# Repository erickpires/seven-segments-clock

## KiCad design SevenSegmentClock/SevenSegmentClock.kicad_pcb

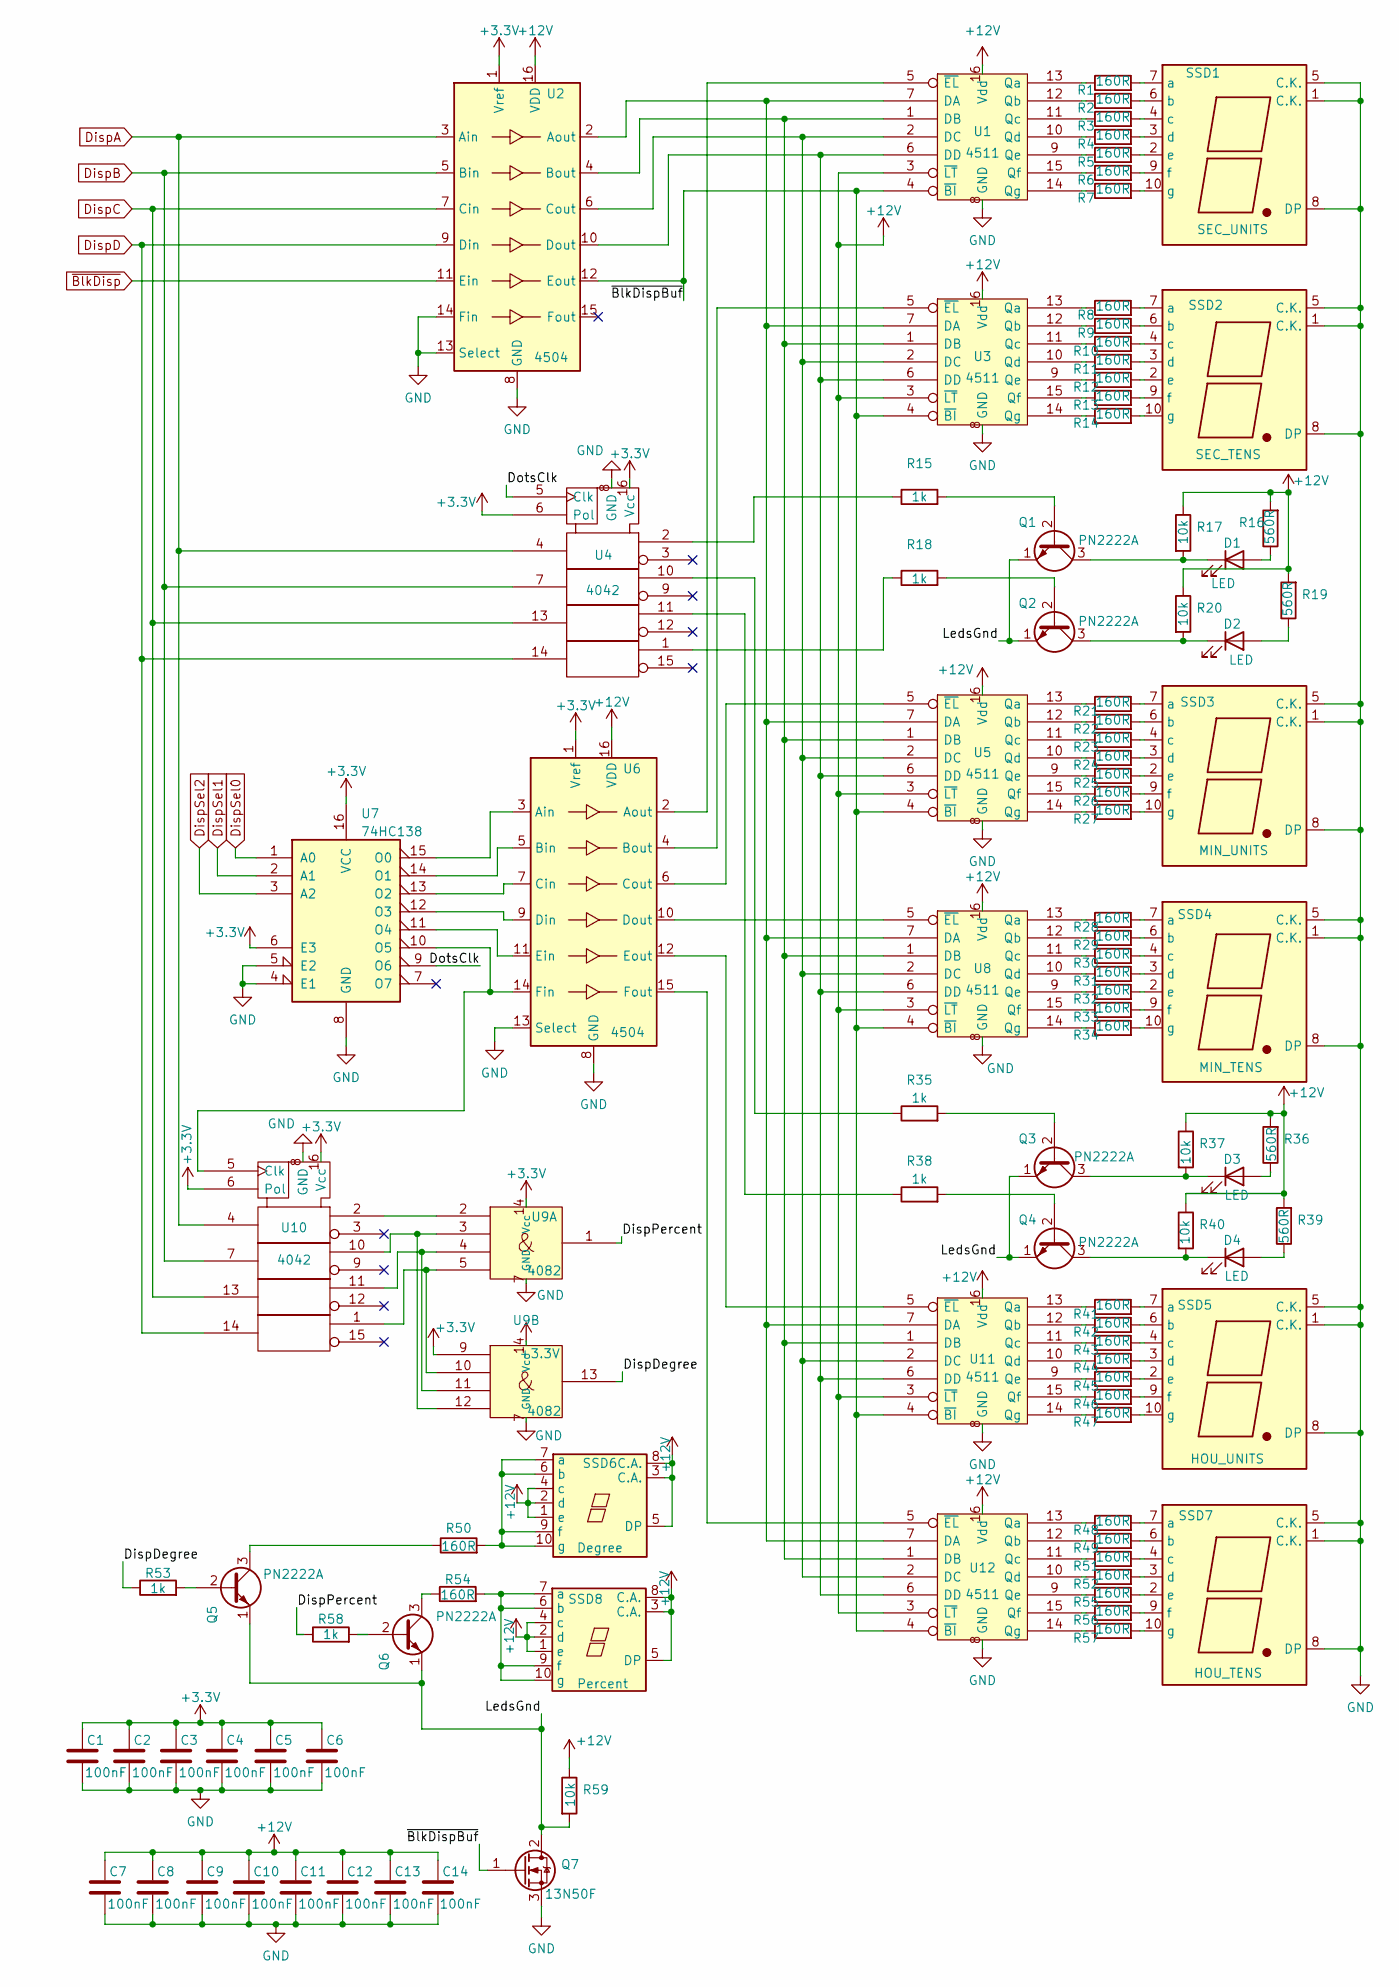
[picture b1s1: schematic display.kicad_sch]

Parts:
C1, C2, C3, C4, C5, C6, C7, C8, C9, C10, C11, C12, C13, C14: 100nF; C_1206_3216Metric_Pad1.33x1.80mm_HandSolder
D1, D2, D3, D4: LED; LED_D5.0mm
Q1, Q2, Q3, Q4, Q5, Q6: PN2222A; TO-92_Inline
Q7: 13N50F; TO-220-3_Vertical
R1, R2, R3, R4, R5, R6, R7, R8, R9, R10, R11, R12, R13, R14, R21, R22, R23, R24, R25, R26, R27, R28, R29, R30, R31, R32, R33, R34, R41, R42, R43, R44, R45, R46, R47, R48, R49, R50, R51, R52, R54, R55, R56, R57: 160R; R_1206_3216Metric_Pad1.30x1.75mm_HandSolder
R15, R18, R35, R38, R53, R58: 1k; R_1206_3216Metric_Pad1.30x1.75mm_HandSolder
R16, R19, R36, R39: 560R; R_Axial_DIN0207_L6.3mm_D2.5mm_P10.16mm_Horizontal
R17, R20, R37, R40, R59: 10k; R_Axial_DIN0207_L6.3mm_D2.5mm_P10.16mm_Horizontal
SSD1: SEC_UNITS; LSD230A
SSD2: SEC_TENS; LSD230A
SSD3: MIN_UNITS; LSD230A
SSD4: MIN_TENS; LSD230A
SSD5: HOU_UNITS; LSD230A
SSD6: Degree; 7SegmentLED_LTS6760_LTS6780
SSD7: HOU_TENS; LSD230A
SSD8: Percent; 7SegmentLED_LTS6760_LTS6780
U1, U3, U5, U8, U11, U12: 4511; SOIC-16_3.9x9.9mm_P1.27mm
U2, U6: 4504; SOIC-16_3.9x9.9mm_P1.27mm
U4, U10: 4042; DIP-16_W7.62mm_Socket_LongPads
U7: 74HC138; SOIC-16_3.9x9.9mm_P1.27mm
U9: 4082; DIP-14_W7.62mm_Socket_LongPads

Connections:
+3.3V: C1.1, C2.1, C3.1, C4.1, C5.1, C6.1, U2.1 (Vref), U4.6 (Pol), U4.16 (Vcc), U6.1 (Vref), U7.6 (E3), U7.16 (VCC), U9.9, U9.14 (Vcc), U10.6 (Pol), U10.16 (Vcc); also elsewhere on the board
+12V: C7.1, C8.1, C9.1, C10.1, C11.1, C12.1, C13.1, C14.1, R16.2, R17.1, R19.2, R20.1, R36.2, R37.1, R39.2, R40.1, R59.1, SSD6.1 (e), SSD6.2 (d), SSD6.3 (C.A.), SSD6.4 (c), SSD6.5 (DP), SSD6.8 (C.A.), SSD8.1 (e), SSD8.2 (d), SSD8.3 (C.A.), SSD8.4 (c), SSD8.5 (DP), SSD8.8 (C.A.), U1.3 (~LT), U1.16 (Vdd), U2.16 (VDD), U3.3 (~LT), U3.16 (Vdd), U5.3 (~LT), U5.16 (Vdd), U6.16 (VDD), U8.3 (~LT), U8.16 (Vdd), U11.3 (~LT), U11.16 (Vdd), U12.3 (~LT), U12.16 (Vdd); also elsewhere on the board
/Display/DotsClk: U4.5 (Clk), U7.9 (O6)
/Display/LedsGnd: Q1.1 (E), Q2.1 (E), Q3.1 (E), Q4.1 (E), Q5.1 (E), Q6.1 (E), Q7.2 (D), R59.2
/Display/~BlkDispBuf: Q7.1 (G), U1.4 (~BI), U2.12 (Eout), U3.4 (~BI), U5.4 (~BI), U8.4 (~BI), U11.4 (~BI), U12.4 (~BI)
DispA: U2.3 (Ain), U4.4, U10.4; also elsewhere on the board
DispB: U2.5 (Bin), U4.7, U10.7; also elsewhere on the board
DispC: U2.7 (Cin), U4.13, U10.13; also elsewhere on the board
DispD: U2.9 (Din), U4.14, U10.14; also elsewhere on the board
DispSel0: U7.1 (A0); also elsewhere on the board
DispSel1: U7.2 (A1); also elsewhere on the board
DispSel2: U7.3 (A2); also elsewhere on the board
GND: C1.2, C2.2, C3.2, C4.2, C5.2, C6.2, C7.2, C8.2, C9.2, C10.2, C11.2, C12.2, C13.2, C14.2, Q7.3 (S), SSD1.1 (C.K.), SSD1.5 (C.K.), SSD1.8 (DP), SSD2.1 (C.K.), SSD2.5 (C.K.), SSD2.8 (DP), SSD3.1 (C.K.), SSD3.5 (C.K.), SSD3.8 (DP), SSD4.1 (C.K.), SSD4.5 (C.K.), SSD4.8 (DP), SSD5.1 (C.K.), SSD5.5 (C.K.), SSD5.8 (DP), SSD7.1 (C.K.), SSD7.5 (C.K.), SSD7.8 (DP), U1.8 (GND), U2.8 (GND), U2.13 (Select), U2.14 (Fin), U3.8 (GND), U4.8 (GND), U5.8 (GND), U6.8 (GND), U6.13 (Select), U7.4 (E1), U7.5 (E2), U7.8 (GND), U8.8 (GND), U9.7 (GND), U10.8 (GND), U11.8 (GND), U12.8 (GND); also elsewhere on the board
unnamed: D1.1 (K), Q1.3 (C), R17.2
unnamed: D1.2 (A), R16.1
unnamed: D2.1 (K), Q2.3 (C), R20.2
unnamed: D2.2 (A), R19.1
unnamed: D3.1 (K), Q3.3 (C), R37.2
unnamed: D3.2 (A), R36.1
unnamed: D4.1 (K), Q4.3 (C), R40.2
unnamed: D4.2 (A), R39.1
unnamed: Q1.2 (B), R15.2
unnamed: Q2.2 (B), R18.2
unnamed: Q3.2 (B), R35.2
unnamed: Q4.2 (B), R38.2
unnamed: Q5.2 (B), R53.2
unnamed: Q5.3 (C), R50.1
unnamed: Q6.2 (B), R58.2
unnamed: Q6.3 (C), R54.1
unnamed: R1.1, U1.13 (Qa)
unnamed: R1.2, SSD1.7 (a)
unnamed: R2.1, U1.12 (Qb)
unnamed: R2.2, SSD1.6 (b)
unnamed: R3.1, U1.11 (Qc)
unnamed: R3.2, SSD1.4 (c)
unnamed: R4.1, U1.10 (Qd)
unnamed: R4.2, SSD1.3 (d)
unnamed: R5.1, U1.9 (Qe)
unnamed: R5.2, SSD1.2 (e)
unnamed: R6.1, U1.15 (Qf)
unnamed: R6.2, SSD1.9 (f)
unnamed: R7.1, U1.14 (Qg)
unnamed: R7.2, SSD1.10 (g)
unnamed: R8.1, U3.13 (Qa)
unnamed: R8.2, SSD2.7 (a)
unnamed: R9.1, U3.12 (Qb)
unnamed: R9.2, SSD2.6 (b)
unnamed: R10.1, U3.11 (Qc)
unnamed: R10.2, SSD2.4 (c)
unnamed: R11.1, U3.10 (Qd)
unnamed: R11.2, SSD2.3 (d)
unnamed: R12.1, U3.9 (Qe)
unnamed: R12.2, SSD2.2 (e)
unnamed: R13.1, U3.15 (Qf)
unnamed: R13.2, SSD2.9 (f)
unnamed: R14.1, U3.14 (Qg)
unnamed: R14.2, SSD2.10 (g)
unnamed: R15.1, U4.2
unnamed: R18.1, U4.1
unnamed: R21.1, U5.13 (Qa)
unnamed: R21.2, SSD3.7 (a)
unnamed: R22.1, U5.12 (Qb)
unnamed: R22.2, SSD3.6 (b)
unnamed: R23.1, U5.11 (Qc)
unnamed: R23.2, SSD3.4 (c)
unnamed: R24.1, U5.10 (Qd)
unnamed: R24.2, SSD3.3 (d)
unnamed: R25.1, U5.9 (Qe)
unnamed: R25.2, SSD3.2 (e)
unnamed: R26.1, U5.15 (Qf)
unnamed: R26.2, SSD3.9 (f)
unnamed: R27.1, U5.14 (Qg)
unnamed: R27.2, SSD3.10 (g)
unnamed: R28.1, U8.13 (Qa)
unnamed: R28.2, SSD4.7 (a)
unnamed: R29.1, U8.12 (Qb)
unnamed: R29.2, SSD4.6 (b)
unnamed: R30.1, U8.11 (Qc)
unnamed: R30.2, SSD4.4 (c)
unnamed: R31.1, U8.10 (Qd)
unnamed: R31.2, SSD4.3 (d)
unnamed: R32.1, U8.9 (Qe)
unnamed: R32.2, SSD4.2 (e)
unnamed: R33.1, U8.15 (Qf)
unnamed: R33.2, SSD4.9 (f)
unnamed: R34.1, U8.14 (Qg)
unnamed: R34.2, SSD4.10 (g)
unnamed: R35.1, U4.10
unnamed: R38.1, U4.11
unnamed: R41.1, U11.13 (Qa)
unnamed: R41.2, SSD5.7 (a)
unnamed: R42.1, U11.12 (Qb)
unnamed: R42.2, SSD5.6 (b)
unnamed: R43.1, U11.11 (Qc)
unnamed: R43.2, SSD5.4 (c)
unnamed: R44.1, U11.10 (Qd)
unnamed: R44.2, SSD5.3 (d)
unnamed: R45.1, U11.9 (Qe)
unnamed: R45.2, SSD5.2 (e)
unnamed: R46.1, U11.15 (Qf)
unnamed: R46.2, SSD5.9 (f)
unnamed: R47.1, U11.14 (Qg)
unnamed: R47.2, SSD5.10 (g)
unnamed: R48.1, U12.13 (Qa)
unnamed: R48.2, SSD7.7 (a)
unnamed: R49.1, U12.12 (Qb)
unnamed: R49.2, SSD7.6 (b)
unnamed: R50.2, SSD6.6 (b), SSD6.7 (a), SSD6.9 (f), SSD6.10 (g)
unnamed: R51.1, U12.11 (Qc)
unnamed: R51.2, SSD7.4 (c)
unnamed: R52.1, U12.10 (Qd)
unnamed: R52.2, SSD7.3 (d)
unnamed: R54.2, SSD8.6 (b), SSD8.7 (a), SSD8.9 (f), SSD8.10 (g)
unnamed: R55.1, U12.9 (Qe)
unnamed: R55.2, SSD7.2 (e)
unnamed: R56.1, U12.15 (Qf)
unnamed: R56.2, SSD7.9 (f)
unnamed: R57.1, U12.14 (Qg)
unnamed: R57.2, SSD7.10 (g)
unnamed: U1.1 (DB), U2.4 (Bout), U3.1 (DB), U5.1 (DB), U8.1 (DB), U11.1 (DB), U12.1 (DB)
unnamed: U1.2 (DC), U2.6 (Cout), U3.2 (DC), U5.2 (DC), U8.2 (DC), U11.2 (DC), U12.2 (DC)
unnamed: U1.5 (~EL), U6.2 (Aout)
unnamed: U1.6 (DD), U2.10 (Dout), U3.6 (DD), U5.6 (DD), U8.6 (DD), U11.6 (DD), U12.6 (DD)
unnamed: U1.7 (DA), U2.2 (Aout), U3.7 (DA), U5.7 (DA), U8.7 (DA), U11.7 (DA), U12.7 (DA)
unnamed: U3.5 (~EL), U6.4 (Bout)
unnamed: U5.5 (~EL), U6.6 (Cout)
unnamed: U6.3 (Ain), U7.15 (O0)
unnamed: U6.5 (Bin), U7.14 (O1)
unnamed: U6.7 (Cin), U7.13 (O2)
unnamed: U6.9 (Din), U7.12 (O3)
unnamed: U6.10 (Dout), U8.5 (~EL)
unnamed: U6.11 (Ein), U7.11 (O4)
unnamed: U9.5, U9.10, U10.1
unnamed: U9.2, U10.2
unnamed: U6.14 (Fin), U7.10 (O5), U10.5 (Clk)
unnamed: U9.3, U9.12, U10.10
unnamed: U9.4, U9.11, U10.11
unnamed: U6.12 (Eout), U11.5 (~EL)
unnamed: U6.15 (Fout), U12.5 (~EL)
~BlkDisp: U2.11 (Ein); also elsewhere on the board

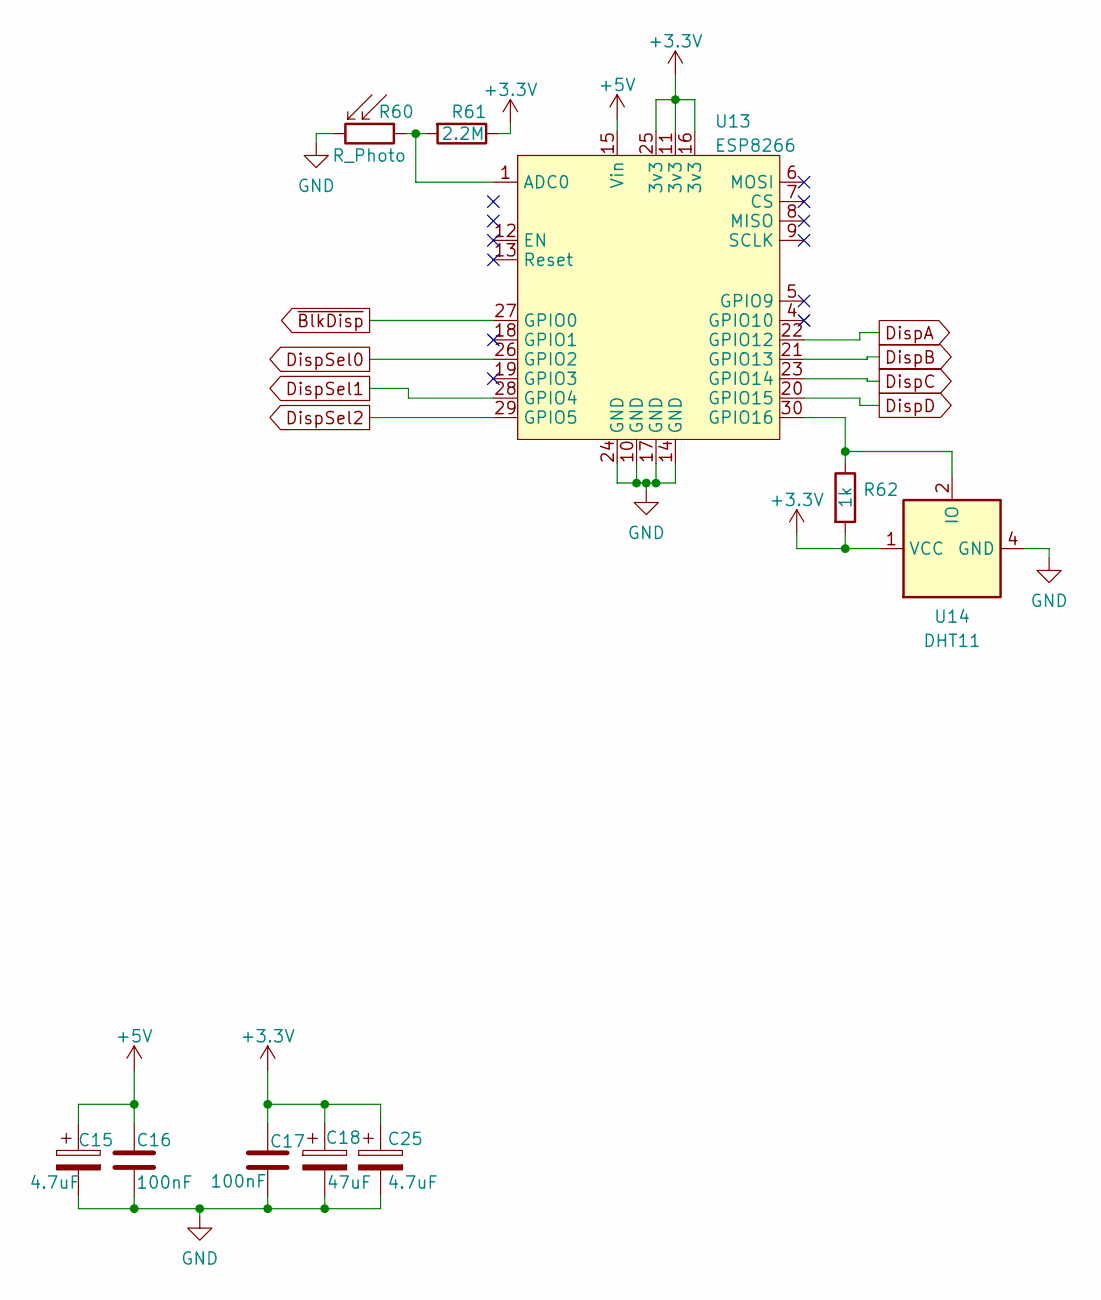
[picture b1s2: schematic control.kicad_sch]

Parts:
C15, C25: 4.7uF; CP_Radial_D6.3mm_P2.50mm
C16, C17: 100nF; C_1206_3216Metric_Pad1.33x1.80mm_HandSolder
C18: 47uF; CP_Radial_D6.3mm_P2.50mm
R60: R_Photo; R_LDR_4.9x4.2mm_P2.54mm_Vertical
R61: 2.2M; R_Axial_DIN0207_L6.3mm_D2.5mm_P10.16mm_Horizontal
R62: 1k; R_1206_3216Metric_Pad1.30x1.75mm_HandSolder
U13: ESP8266; ESP8266 (NodeMCU_12-E)
U14: DHT11; Aosong_DHT11_5.5x12.0_P2.54mm

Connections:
+3.3V: C17.1, C18.1, C25.1, R61.1, R62.2, U13.11 (3v3), U13.16 (3v3), U13.25 (3v3), U14.1 (VCC); also elsewhere on the board
+5V: C15.1, C16.1, U13.15 (Vin); also elsewhere on the board
DispA: U13.22 (GPIO12); also elsewhere on the board
DispB: U13.21 (GPIO13); also elsewhere on the board
DispC: U13.23 (GPIO14); also elsewhere on the board
DispD: U13.20 (GPIO15); also elsewhere on the board
DispSel0: U13.26 (GPIO2); also elsewhere on the board
DispSel1: U13.28 (GPIO4); also elsewhere on the board
DispSel2: U13.29 (GPIO5); also elsewhere on the board
GND: C15.2, C16.2, C17.2, C18.2, C25.2, R60.2, U13.10 (GND), U13.14 (GND), U13.17 (GND), U13.24 (GND), U14.4 (GND); also elsewhere on the board
unnamed: R60.1, R61.2, U13.1 (ADC0)
unnamed: R62.1, U13.30 (GPIO16), U14.2 (IO)
~BlkDisp: U13.27 (GPIO0); also elsewhere on the board

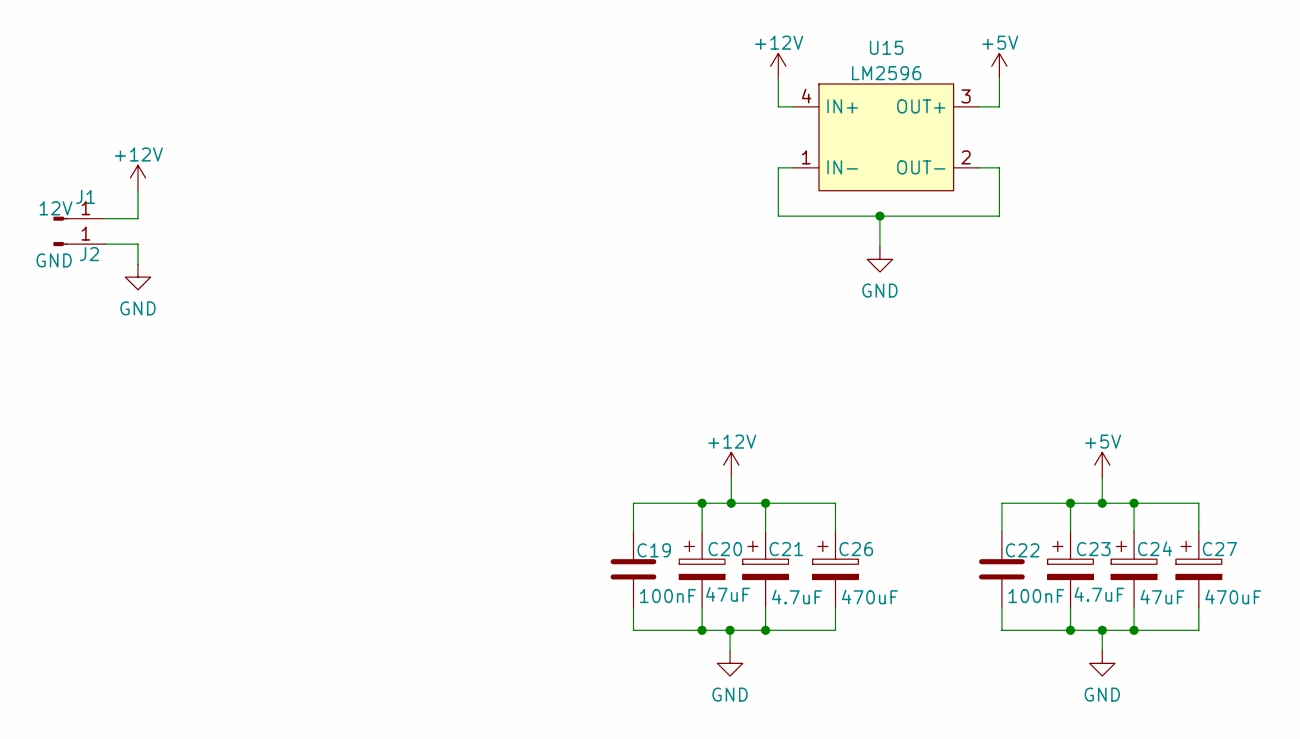
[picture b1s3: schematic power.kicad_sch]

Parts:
C19, C22: 100nF; C_1206_3216Metric_Pad1.33x1.80mm_HandSolder
C20, C24: 47uF; CP_Radial_D6.3mm_P2.50mm
C21, C23: 4.7uF; CP_Radial_D6.3mm_P2.50mm
C26, C27: 470uF; CP_Radial_D10.0mm_P5.00mm
J1: 12V; PinHeader_1x01_P2.54mm_Vertical
J2: GND; PinHeader_1x01_P2.54mm_Vertical
U15: LM2596

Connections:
+5V: C22.1, C23.1, C24.1, C27.1, U15.3 (OUT+); also elsewhere on the board
+12V: C19.1, C20.1, C21.1, C26.1, J1.1, U15.4 (IN+); also elsewhere on the board
GND: C19.2, C20.2, C21.2, C22.2, C23.2, C24.2, C26.2, C27.2, J2.1, U15.1 (IN-), U15.2 (OUT-); also elsewhere on the board

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
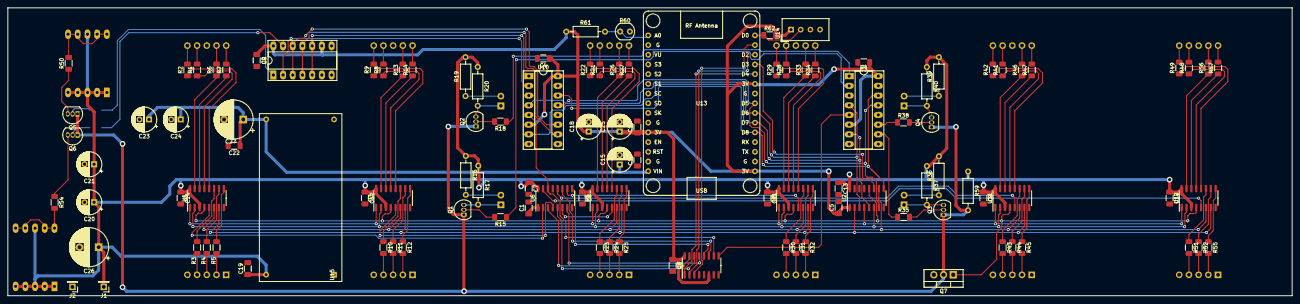
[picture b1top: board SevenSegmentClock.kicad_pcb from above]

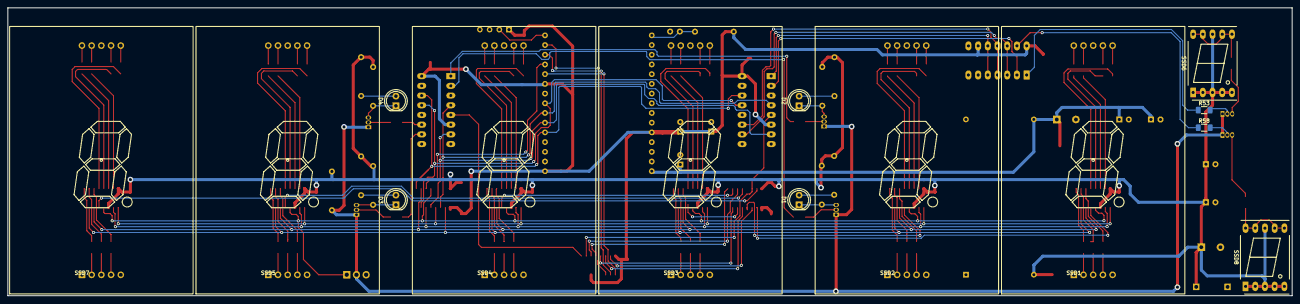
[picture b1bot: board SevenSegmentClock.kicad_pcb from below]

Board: 2 copper layers, 336.1 x 75.3 mm, 125 parts (14 on the bottom side), 145 nets.

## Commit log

2023-02-06 Starting schematic
2024-02-11 NTP code
2024-02-11 Updating BOM
2024-02-11 Modifying code to use direct port manipulation
2024-02-11 Implementing the comunication with the DHT11
2024-02-11 WIP: Configuration server
2024-02-11 Assigning footprints
2024-02-11 Moving the display code to a separate file
2024-02-11 Adding the control schematic and fixing Eletrical Rules Checks
2024-02-11 Adding two more displays to show a degree and a percent symbols
2024-02-11 Using SigmaDelta to implement dimming of the display
2024-02-11 Fixing incorrect footprints
2024-02-11 WIP: PCB design
2024-02-11 The 560R resistor was not available in a SMD package
2024-02-11 Gerber files
2024-02-11 Cleaning up the display code and displaying date, temperature and humidity
2024-02-11 Better routing
2024-02-11 Updating to newer kicad
2024-02-11 Ground fill and DRC fixes
2024-02-11 Fixing the polarity of the CD4042s
2024-02-11 Swapping around percentage and degree indicators
2024-02-11 Fixing the display masks and adding the other digits
2024-02-11 Finishing PCB design
2024-02-11 Transition animation between display updates
2024-02-11 After adding the transition, the display looks better blinking every 2 seconds
2024-02-11 Adding transition animations to the columns indicators
2024-02-11 Cleaning up the code. Removing some debug code and moving the display setup
2024-02-11 We don't need to update the display when both values are the same
2024-02-11 Removing some work-arounds since we can set the display every iteration now
2024-02-11 Moving the blinking behavior back to the main loop
2024-02-11 Moving configuration code to a dedicated file
2024-02-11 Refactoring the configuration server code
2024-02-11 Saving the device configuration in the EEPROM
2024-02-11 Using configuration to set the display brightness
2024-02-20 Passing the sensor pin and the sensor type at the DHT class construction
2024-02-20 Reading the DHT sensor every 2 seconds since even the DHT11 can handle a 0.5Hz refresh rate
2024-02-20 Handling the DHT22 data format
